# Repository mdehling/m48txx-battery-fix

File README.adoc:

= M48TXX Battery Fix
Malte Dehling

:imagesdir: https://raw.githubusercontent.com/mdehling/m48txx-battery-fix/main/img/

:url-gw-48t02: http://www.glitchwrks.com/2017/08/01/gw-48t02-1
:url-tindie-gw48t02: https://www.tindie.com/products/glitchwrks/gw-48t02-1-repair-board-diy-48t02-repair-module/
:url-tindie-gw48t08: https://www.tindie.com/products/glitchwrks/gw-48t08-1-repair-board-module/
:url-nvram-faq: http://www.obsolyte.com/sunFAQ/faq_nvram.html

The M48T02/M48T08 NVRAM chips have builtin batteries and these batteries die
after a couple of years, resulting in the loss of the NVRAM contents.  As a
result, depending on the system in question, the NVRAM may need to be
reprogrammed on every boot.  This module is designed to replace the top half
of the NVRAM chip containing the battery to make it easily replaceable.  The
project is a shameless ripoff of GlitchWorks'.  You can buy their version for
the {url-tindie-gw48t02}[M48T02] and {url-tindie-gw48t08}[M48T08] on Tindie,
and they have more.

By using SMT components, an M48TXX rebuilt with this module is, in fact,
flatter than the original.  Do note, however, that, with a CR2016 installed
the chip is a little wider than before.  Make sure this is not a problem in
your system!

Parts & Assembly
----------------
Besides the battery, the upper half of the M48TXX also contains a 32.768kHz
Crystal.  These are the replacement parts I use:

[%autowidth]
|===
| Designator | Quantity | Description

| Y1         | 1        | ECS-.327-12.5-34QCN-TR
| BT1        | 1        | Linx BAT-HLD-002-SMT
|===

The battery holder is a CR2016 coin cell holder, so obviously you will also
need a CR2016 coin cell to install in it.

Once you assemble the board, it should look something like this:

link:{imagesdir}modules.jpg[image:modules.jpg["Modules",width=32%]]

Rebuilding the Chip
-------------------
Read link:{url-gw-48t02}[GlitchWorks' post on the M48T02].  Make sure to
correctly align pin 1, both when rebuilding the NVRAM and when installing it,
or you *will* kill your NVRAM.

Here are some photos of the rebuilt module installed in a SPARCstation IPC:

link:{imagesdir}in-ss-ipc_1.jpg[image:in-ss-ipc_1.jpg["In a SPARCstation IPC 1",width=32%]]
link:{imagesdir}in-ss-ipc_2.jpg[image:in-ss-ipc_2.jpg["In a SPARCstation IPC 2",width=32%]]

Reprogramming the NVRAM
-----------------------
How to do this depends on the machine the chip is used in.  For SUN's
SPARCstations see the {url-nvram-faq}[NVRAM FAQ].

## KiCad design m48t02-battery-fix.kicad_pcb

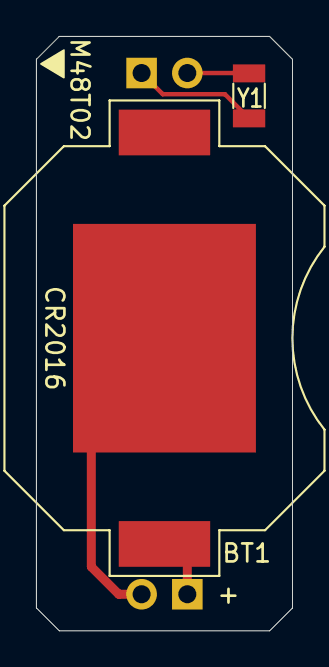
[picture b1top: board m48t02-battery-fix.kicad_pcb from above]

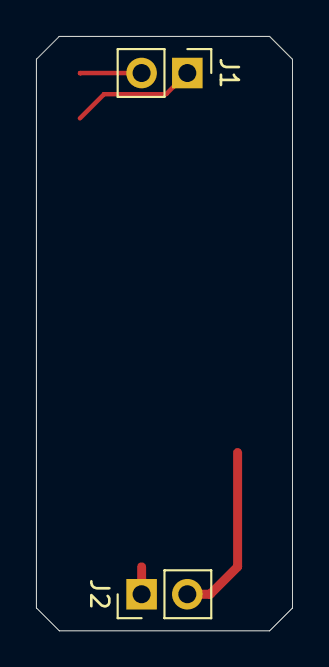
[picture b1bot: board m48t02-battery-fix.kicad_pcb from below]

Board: 2 copper layers, 14.2 x 33.0 mm, 4 parts (2 on the bottom side), 4 nets.

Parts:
BT1: CR2016; BAT-HLD-002-SMT-OTL
J1: OSC; PinHeader_1x02_P2.54mm_Vertical
J2: PWR; PinHeader_1x02_P2.54mm_Vertical
Y1: 31.768kHz; Crystal_SMD_3215-2Pin_3.2x1.5mm

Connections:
unnamed: BT1.1, J2.1
unnamed: BT1.2, J2.2
unnamed: J1.1, Y1.1
unnamed: J1.2, Y1.2

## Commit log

2021-04-23 Update silkscreen
2021-04-24 Add README
2021-04-24 Fix a typo
2021-04-24 Add missing file
2021-04-24 Add photos to instructions
2022-05-27 Update image URLs
